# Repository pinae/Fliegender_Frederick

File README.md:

# Fliegender_Frederick
Flugsimulator-Controller mit Arduino Micro

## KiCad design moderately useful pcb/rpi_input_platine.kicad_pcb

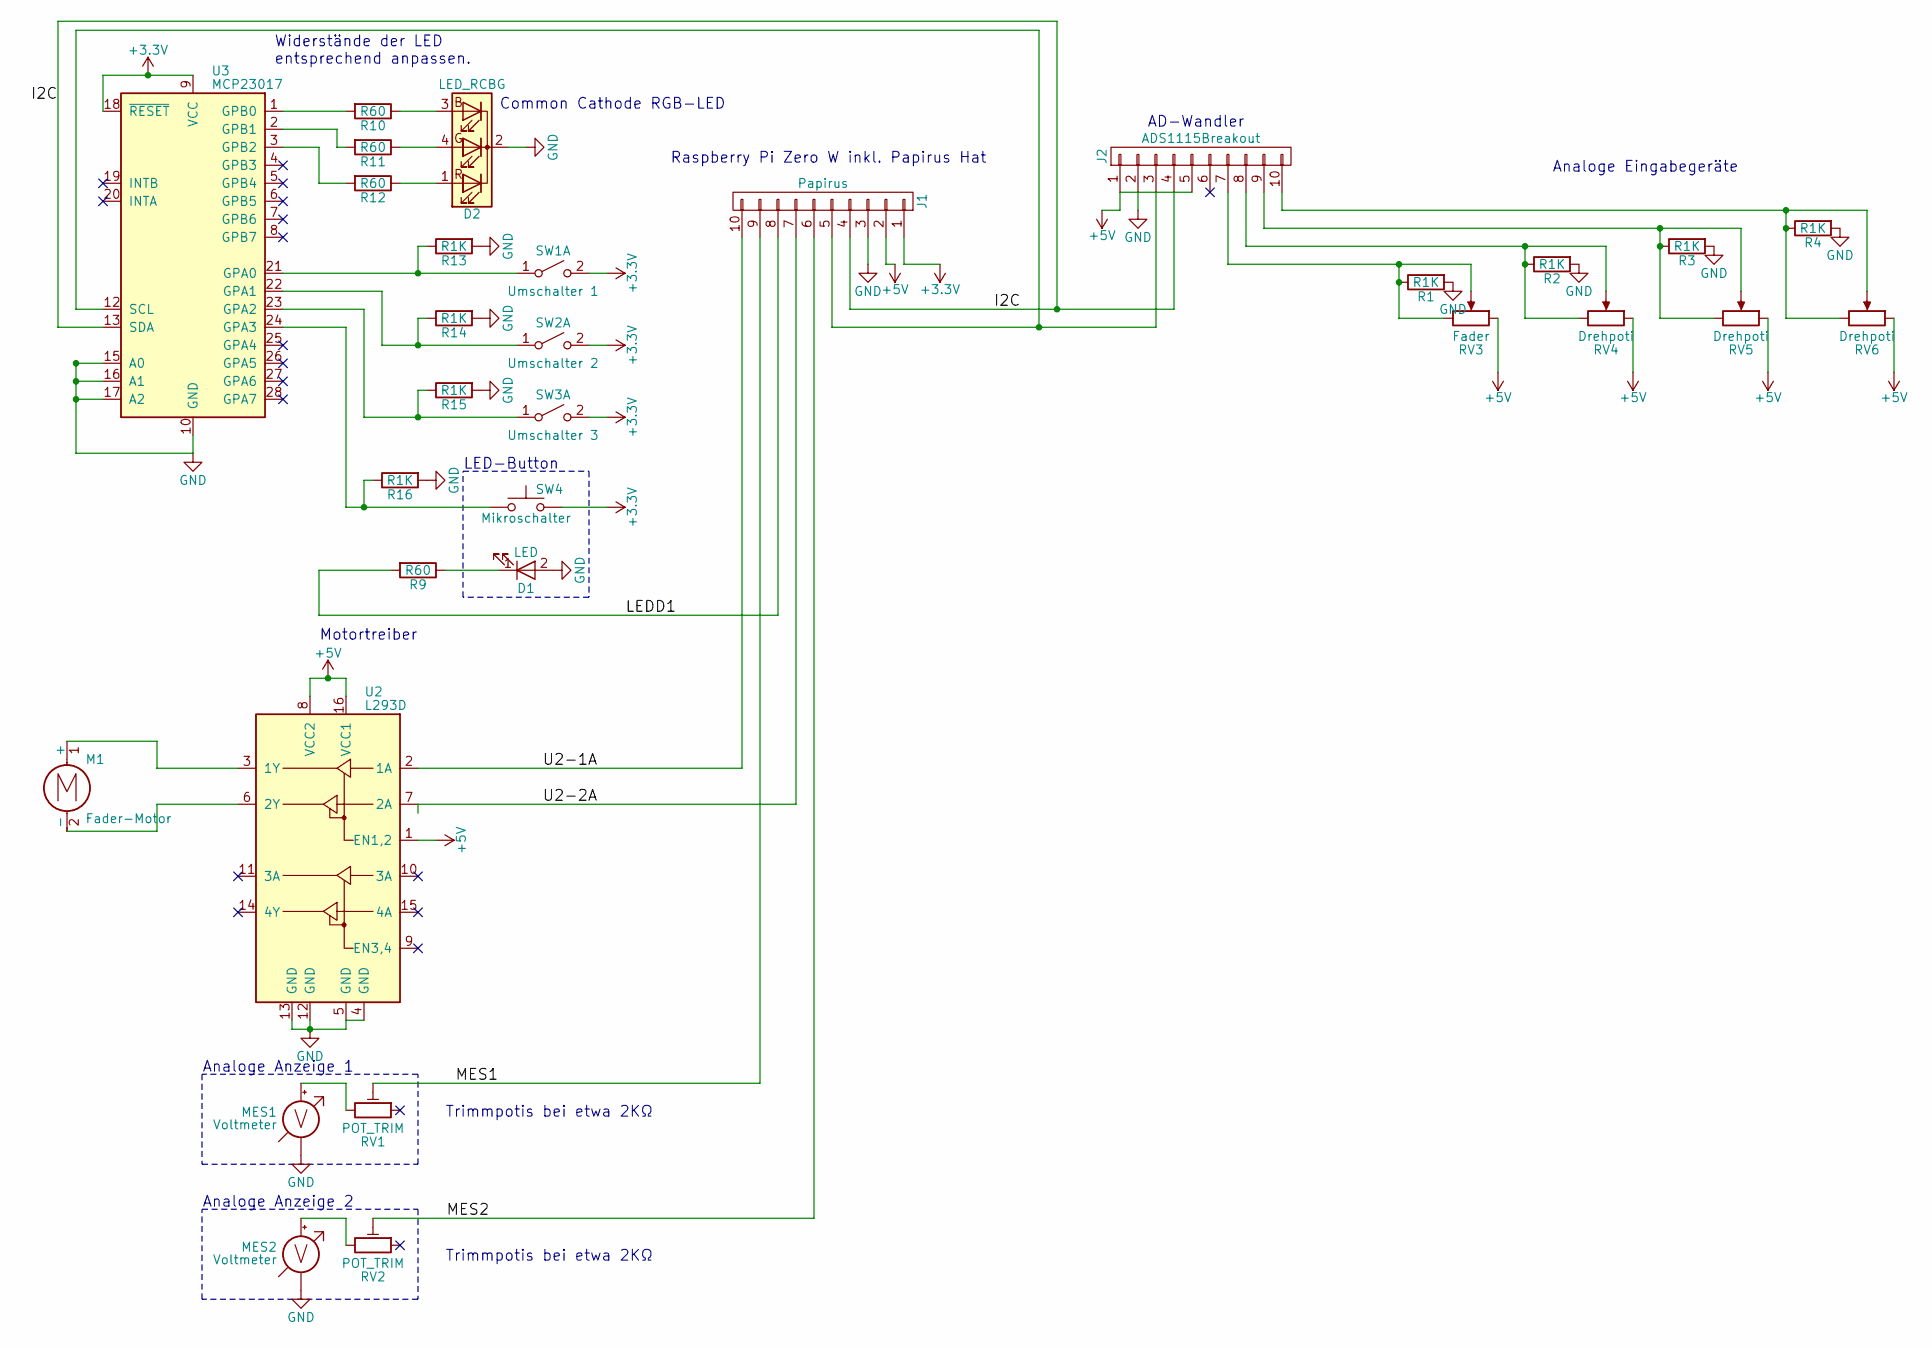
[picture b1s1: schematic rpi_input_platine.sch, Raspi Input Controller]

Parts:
D1: LED; Pin_Header_Straight_1x02_Pitch2.54mm
D2: LED_RCBG; Pin_Header_Straight_1x04_Pitch2.54mm
J1: Papirus; Pin_Header_Straight_1x10_Pitch2.54mm
J2: ADS1115Breakout; Pin_Header_Straight_1x10_Pitch2.54mm
M1: Fader-Motor; Pin_Header_Straight_1x02_Pitch2.54mm
MES1, MES2: Voltmeter; Pin_Header_Straight_1x02_Pitch2.54mm
R1, R2, R3, R4, R13, R14, R15, R16: R1K; R_Axial_DIN0309_L9.0mm_D3.2mm_P12.70mm_Horizontal
R9, R10, R11, R12: R60; R_Axial_DIN0309_L9.0mm_D3.2mm_P12.70mm_Horizontal
RV1, RV2: POT_TRIM; Potentiometer_Trimmer_Piher_PT-6h_Vertical
RV3: Fader; Pin_Header_Straight_1x02_Pitch2.54mm
RV4, RV5, RV6: Drehpoti; Pin_Header_Straight_1x02_Pitch2.54mm
SW1: Umschalter 1; Pin_Header_Straight_1x02_Pitch2.54mm
SW2: Umschalter 2; Pin_Header_Straight_1x02_Pitch2.54mm
SW3: Umschalter 3; Pin_Header_Straight_1x02_Pitch2.54mm
SW4: Mikroschalter; Pin_Header_Straight_1x02_Pitch2.54mm
U2: L293D; DIP-16_W7.62mm_Socket
U3: MCP23017; DIP-28_W7.62mm_Socket

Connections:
+3V3: J1.1 (CN5), SW1.2 (B), SW2.2 (B), SW3.2 (B), SW4.2, U3.9 (VCC), U3.18 (~RESET)
+5V: J1.2 (CN6), J2.1 (GND), J2.5 (ADDR), RV3.1, RV4.1, RV5.1, RV6.1, U2.1 (EN1,2), U2.8 (VCC2), U2.16 (VCC1)
/I2C: J1.4 (CN8), J2.4 (ADR), U3.13 (SDA)
/LEDD1: J1.8 (CN12), R9.2
/MES1: J1.9 (CN15), RV1.2
/MES2: J1.6 (CN10), RV2.2
/U2-1A: J1.10 (CN17), U2.2 (1A)
/U2-2A: J1.7 (CN11), U2.7 (2A)
GND: D1.2 (A), D2.2 (K), J1.3 (CN7), J2.2 (GND), MES1.1 (-), MES2.1 (-), R1.2, R2.2, R3.2, R4.2, R13.2, R14.2, R15.2, R16.2, U2.4 (GND), U2.5 (GND), U2.12 (GND), U2.13 (GND), U3.10 (GND), U3.15 (A0), U3.16 (A1), U3.17 (A2)
unnamed: D1.1 (K), R9.1
unnamed: D2.1 (RA), R12.1
unnamed: D2.3 (BA), R10.1
unnamed: D2.4 (GA), R11.1
unnamed: J1.5 (CN9), J2.3 (SCL), U3.12 (SCL)
unnamed: J2.7 (A0), R1.1, RV3.2, RV3.3
unnamed: J2.8 (A1), R2.1, RV4.2, RV4.3
unnamed: J2.9 (A2), R3.1, RV5.2, RV5.3
unnamed: J2.10 (A3), R4.1, RV6.2, RV6.3
unnamed: M1.1 (+), U2.3 (1Y)
unnamed: M1.2 (-), U2.6 (2Y)
unnamed: MES1.2 (+), RV1.3
unnamed: MES2.2 (+), RV2.3
unnamed: R10.2, U3.1 (GPB0)
unnamed: R11.2, U3.2 (GPB1)
unnamed: R12.2, U3.3 (GPB2)
unnamed: R13.1, SW1.1 (A), U3.21 (GPA0)
unnamed: R14.1, SW2.1 (A), U3.22 (GPA1)
unnamed: R15.1, SW3.1 (A), U3.23 (GPA2)
unnamed: R16.1, SW4.1, U3.24 (GPA3)

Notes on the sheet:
LED-Button
Analoge Anzeige 1
Analoge Anzeige 2
Raspberry Pi Zero W inkl. Papirus Hat
AD-Wandler
Motortreiber
Analoge Eingabegeräte
Trimmpotis bei etwa 2KΩ
Widerstände der LED entsprechend anpassen.
Common Cathode RGB-LED

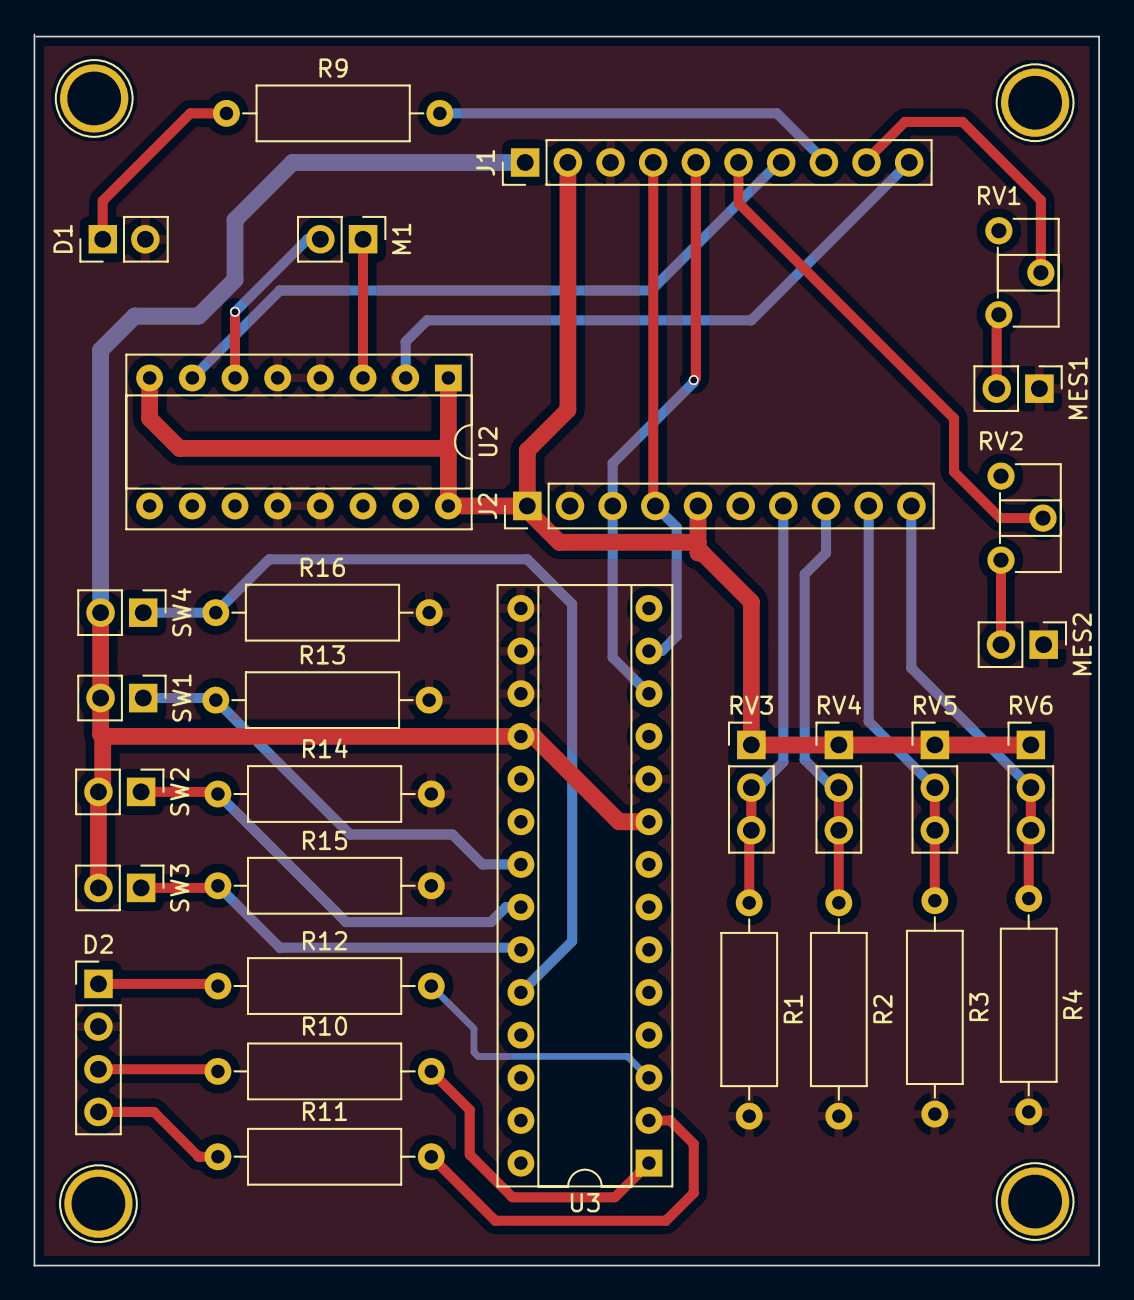
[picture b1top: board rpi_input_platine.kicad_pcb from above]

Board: 2 copper layers, 63.4 x 73.3 mm, 31 parts (0 on the bottom side), 29 nets.

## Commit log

2020-09-17 project started
2020-09-17 first experiments
2020-09-18 software debounce for the switches
2020-09-18 software debounce and reading for the flaps
2020-09-18 software debounce and reading for the landing gear
2020-09-18 correct pins for the trim wheel
2020-09-18 introduced the debounce timer for faster loop iterations
2020-09-19 detecting switch toggles and executing functions on toggle
2020-09-19 detecting landing gear and flaps changes
2020-09-21 debugged toggling switch states. It's fixed now and the readirngs are stable.
2020-09-21 send keypresses on switch toggles
2020-09-24 gerber files and KiCAD project for the not really perfectly matching pcb − feel free to modify...
